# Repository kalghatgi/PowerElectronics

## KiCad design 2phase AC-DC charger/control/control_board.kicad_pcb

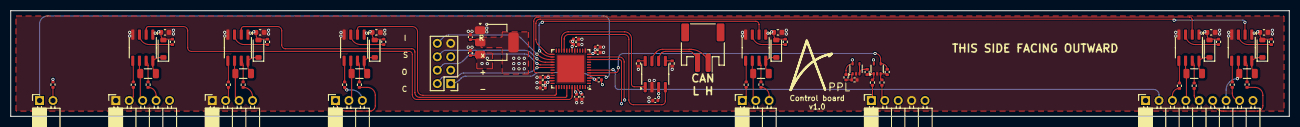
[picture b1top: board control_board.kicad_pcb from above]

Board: 4 copper layers, 242.0 x 20.0 mm, 78 parts (0 on the bottom side), 75 nets.

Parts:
C1, C2, C3, C4, C5, C6: 100nF, >=25V; C_1206_3216Metric
C7, C8, C14, C15, C16, C17, C18: 1uF, >=6.3V; C_0402_1005Metric
C9, C10: 10uF, >=6.3V; C_0402_1005Metric
C11, C13: 100nF, >=6.3V; C_0402_1005Metric
C12: 4.7uF, >=6.3V; C_0402_1005Metric
C19, C20, C21, C22, C23, C24: 10uF, >=25V; C_0603_1608Metric
D1, D2, D3, D4, D5, D6: Vr>=600V, If>=1A; D_SOD-123
IC1: F2800137RGZR; QFN-48-1EP_7x7mm_P0.5mm_EP5.1x5.1mm
J1: Conn_01x04_Socket; PinSocket_1x04_P2.54mm_Horizontal
J2, J6: Conn_01x04_Socket; PinSocket_1x05_P2.54mm_Horizontal
J3, J4: Conn_01x04_Socket; PinSocket_1x03_P2.54mm_Horizontal
J5: Conn_01x04_Socket; PinSocket_1x02_P2.54mm_Horizontal
J7: Conn_01x04_Socket; PinSocket_1x09_P2.54mm_Horizontal
J8: Conn_01x02_Pin; JST_PH_S2B-PH-SM4-TB_1x02-1MP_P2.00mm_Horizontal
J9: Conn_02x04_Counter_Clockwise; PinHeader_2x04_P2.54mm_Vertical
R1, R2, R3, R4, R5, R6, R7, R20, R21, R22, R23, R24, R25, R26, R27, R28: 10K, 62.5mW, 0402; R_0402_1005Metric
R8, R9, R10, R11, R12, R13, R14, R15, R16, R17, R18, R19: 4R, 62.5mW, 0402; R_0402_1005Metric
U1, U2, U3, U4, U5, U6: IR2104; SOIC-8_3.9x4.9mm_P1.27mm
U7: TCAN3414DR; SOIC-8_3.9x4.9mm_P1.27mm
U8: LD1117S12TR_SOT223; SOT-223-3_TabPin2
U9, U10: LMV321; SOT-353_SC-70-5

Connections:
+1.2V: C10.1, C15.1, C16.1, C17.1, C18.1, IC1.18 (VDDA), IC1.34 (VDDIO), IC1.45 (VDDIO), U8.2 (VO)
+3.3V: C7.1, C8.1, C9.1, C11.1, C12.1, C13.1, C14.1, IC1.12 (VREFHI), IC1.35 (VDD), IC1.44 (VDD), J6.3, J9.5, R7.1, R20.1, R21.1, U7.3 (VCC), U8.3 (VI), U9.5 (V+), U10.5 (V+)
+12V: C19.1, C20.1, C21.1, C22.1, C23.1, C24.1, D1.2 (A), D2.2 (A), D3.2 (A), D4.2 (A), D5.2 (A), D6.2 (A), J6.5, R1.1, R2.1, R3.1, R4.1, R5.1, R6.1, U1.1 (VCC), U2.1 (VCC), U3.1 (VCC), U4.1 (VCC), U5.1 (VCC), U6.1 (VCC)
/CAN_H: J8.1, U7.7 (CANH)
/CAN_L: J8.2, U7.6 (CANL)
/CAN_Rx: IC1.21 (A10/C10/GPIO230), U7.4 (RXD)
/CAN_Tx: IC1.22 (A19/C19/GPIO13), U7.1 (TXD)
/I_p: IC1.5 (A3/C5/GPIO242), R24.1, U10.4
/L_in: IC1.32 (GPIO18X2), U6.2 (IN)
/N_in: IC1.25 (GPIO16), U5.2 (IN)
/TCK: IC1.27 (TCK), J9.8
/TDI: IC1.30 (GPIO35/TDI), J9.2
/TDO: IC1.28 (GPIO37/TDO), J9.6
/TMS: IC1.29 (TMS), J9.4
/pA_in: IC1.26 (GPIO24), U3.2 (IN)
/pB_in: IC1.37 (GPIO4), U4.2 (IN)
/sA_in: IC1.43 (GPIO7), U1.2 (IN)
/sB_in: IC1.41 (GPIO0), U2.2 (IN)
/~RST: IC1.3 (XRSN), J9.1, R7.2
GND0: C7.2, C8.2, C9.2, C10.2, C11.2, C12.2, C13.2, C14.2, C15.2, C16.2, C17.2, C18.2, C19.2, C20.2, C21.2, C22.2, C23.2, C24.2, IC1.13 (VREFLO), IC1.17 (VSSA), IC1.49 (VSS), J1.1, J2.1, J6.4, J9.7, R22.2, R27.2, R28.2, U1.4 (COM), U2.4 (COM), U3.4 (COM), U4.4 (COM), U5.4 (COM), U6.4 (COM), U7.2 (GND), U8.1 (GND), U9.2 (V-), U10.2 (V-)
Ip_+: J6.2, R25.2
Ip_-: J6.1, R26.2
L_HG: J7.5, R13.1
L_HS: C6.2, J7.4, U6.6 (VS)
L_LG: J7.3, R16.1
N_HG: J7.6, R12.1
N_HS: C5.2, J7.7, U5.6 (VS)
N_LG: J7.8, R17.1
unnamed: C1.1, D1.1 (K), U1.8 (VB)
unnamed: C2.1, D2.1 (K), U2.8 (VB)
unnamed: C3.1, D3.1 (K), U3.8 (VB)
unnamed: C4.1, D4.1 (K), U4.8 (VB)
unnamed: C5.1, D5.1 (K), U5.8 (VB)
unnamed: C6.1, D6.1 (K), U6.8 (VB)
unnamed: R9.2, U1.7 (HO)
unnamed: R14.2, U1.5 (LO)
unnamed: R1.2, U1.3 (~SD)
unnamed: R8.2, U2.7 (HO)
unnamed: R19.2, U2.5 (LO)
unnamed: R2.2, U2.3 (~SD)
unnamed: R10.2, U3.7 (HO)
unnamed: R15.2, U3.5 (LO)
unnamed: R3.2, U3.3 (~SD)
unnamed: R11.2, U4.7 (HO)
unnamed: R18.2, U4.5 (LO)
unnamed: R4.2, U4.3 (~SD)
unnamed: R12.2, U5.7 (HO)
unnamed: R17.2, U5.5 (LO)
unnamed: R5.2, U5.3 (~SD)
unnamed: R13.2, U6.7 (HO)
unnamed: R16.2, U6.5 (LO)
unnamed: R6.2, U6.3 (~SD)
unnamed: R27.1, U7.5 (SHDN)
unnamed: R28.1, U7.8 (STB)
unnamed: R21.2, R22.1, U9.1 (+)
unnamed: R23.2, U9.3 (-), U9.4
unnamed: R23.1, R26.1, U10.1 (+)
unnamed: R24.2, R25.1, U10.3 (-)
V_batt_opto_in: J5.2, R20.2
V_battery: IC1.4 (A6/C6/GPIO226/GPIO228), J5.1
V_line: IC1.11 (A0/C15/CMP1_DACL), J7.1
V_neutral: IC1.10 (A1), J7.9
V_p: IC1.6 (A2/C9/GPIO224), J7.2
pA_HG: J3.3, R10.1
pA_HS: C3.2, J3.2, U3.6 (VS)
pA_LG: J3.1, R15.1
pB_HG: J4.1, R11.1
pB_HS: C4.2, J4.2, U4.6 (VS)
pB_LG: J4.3, R18.1
sA_HG: J2.4, R9.1
sA_HS: C1.2, J2.3, U1.6 (VS)
sA_LG: J2.2, R14.1
sB_HG: J1.4, R8.1
sB_HS: C2.2, J1.3, U2.6 (VS)
sB_LG: J1.2, R19.1

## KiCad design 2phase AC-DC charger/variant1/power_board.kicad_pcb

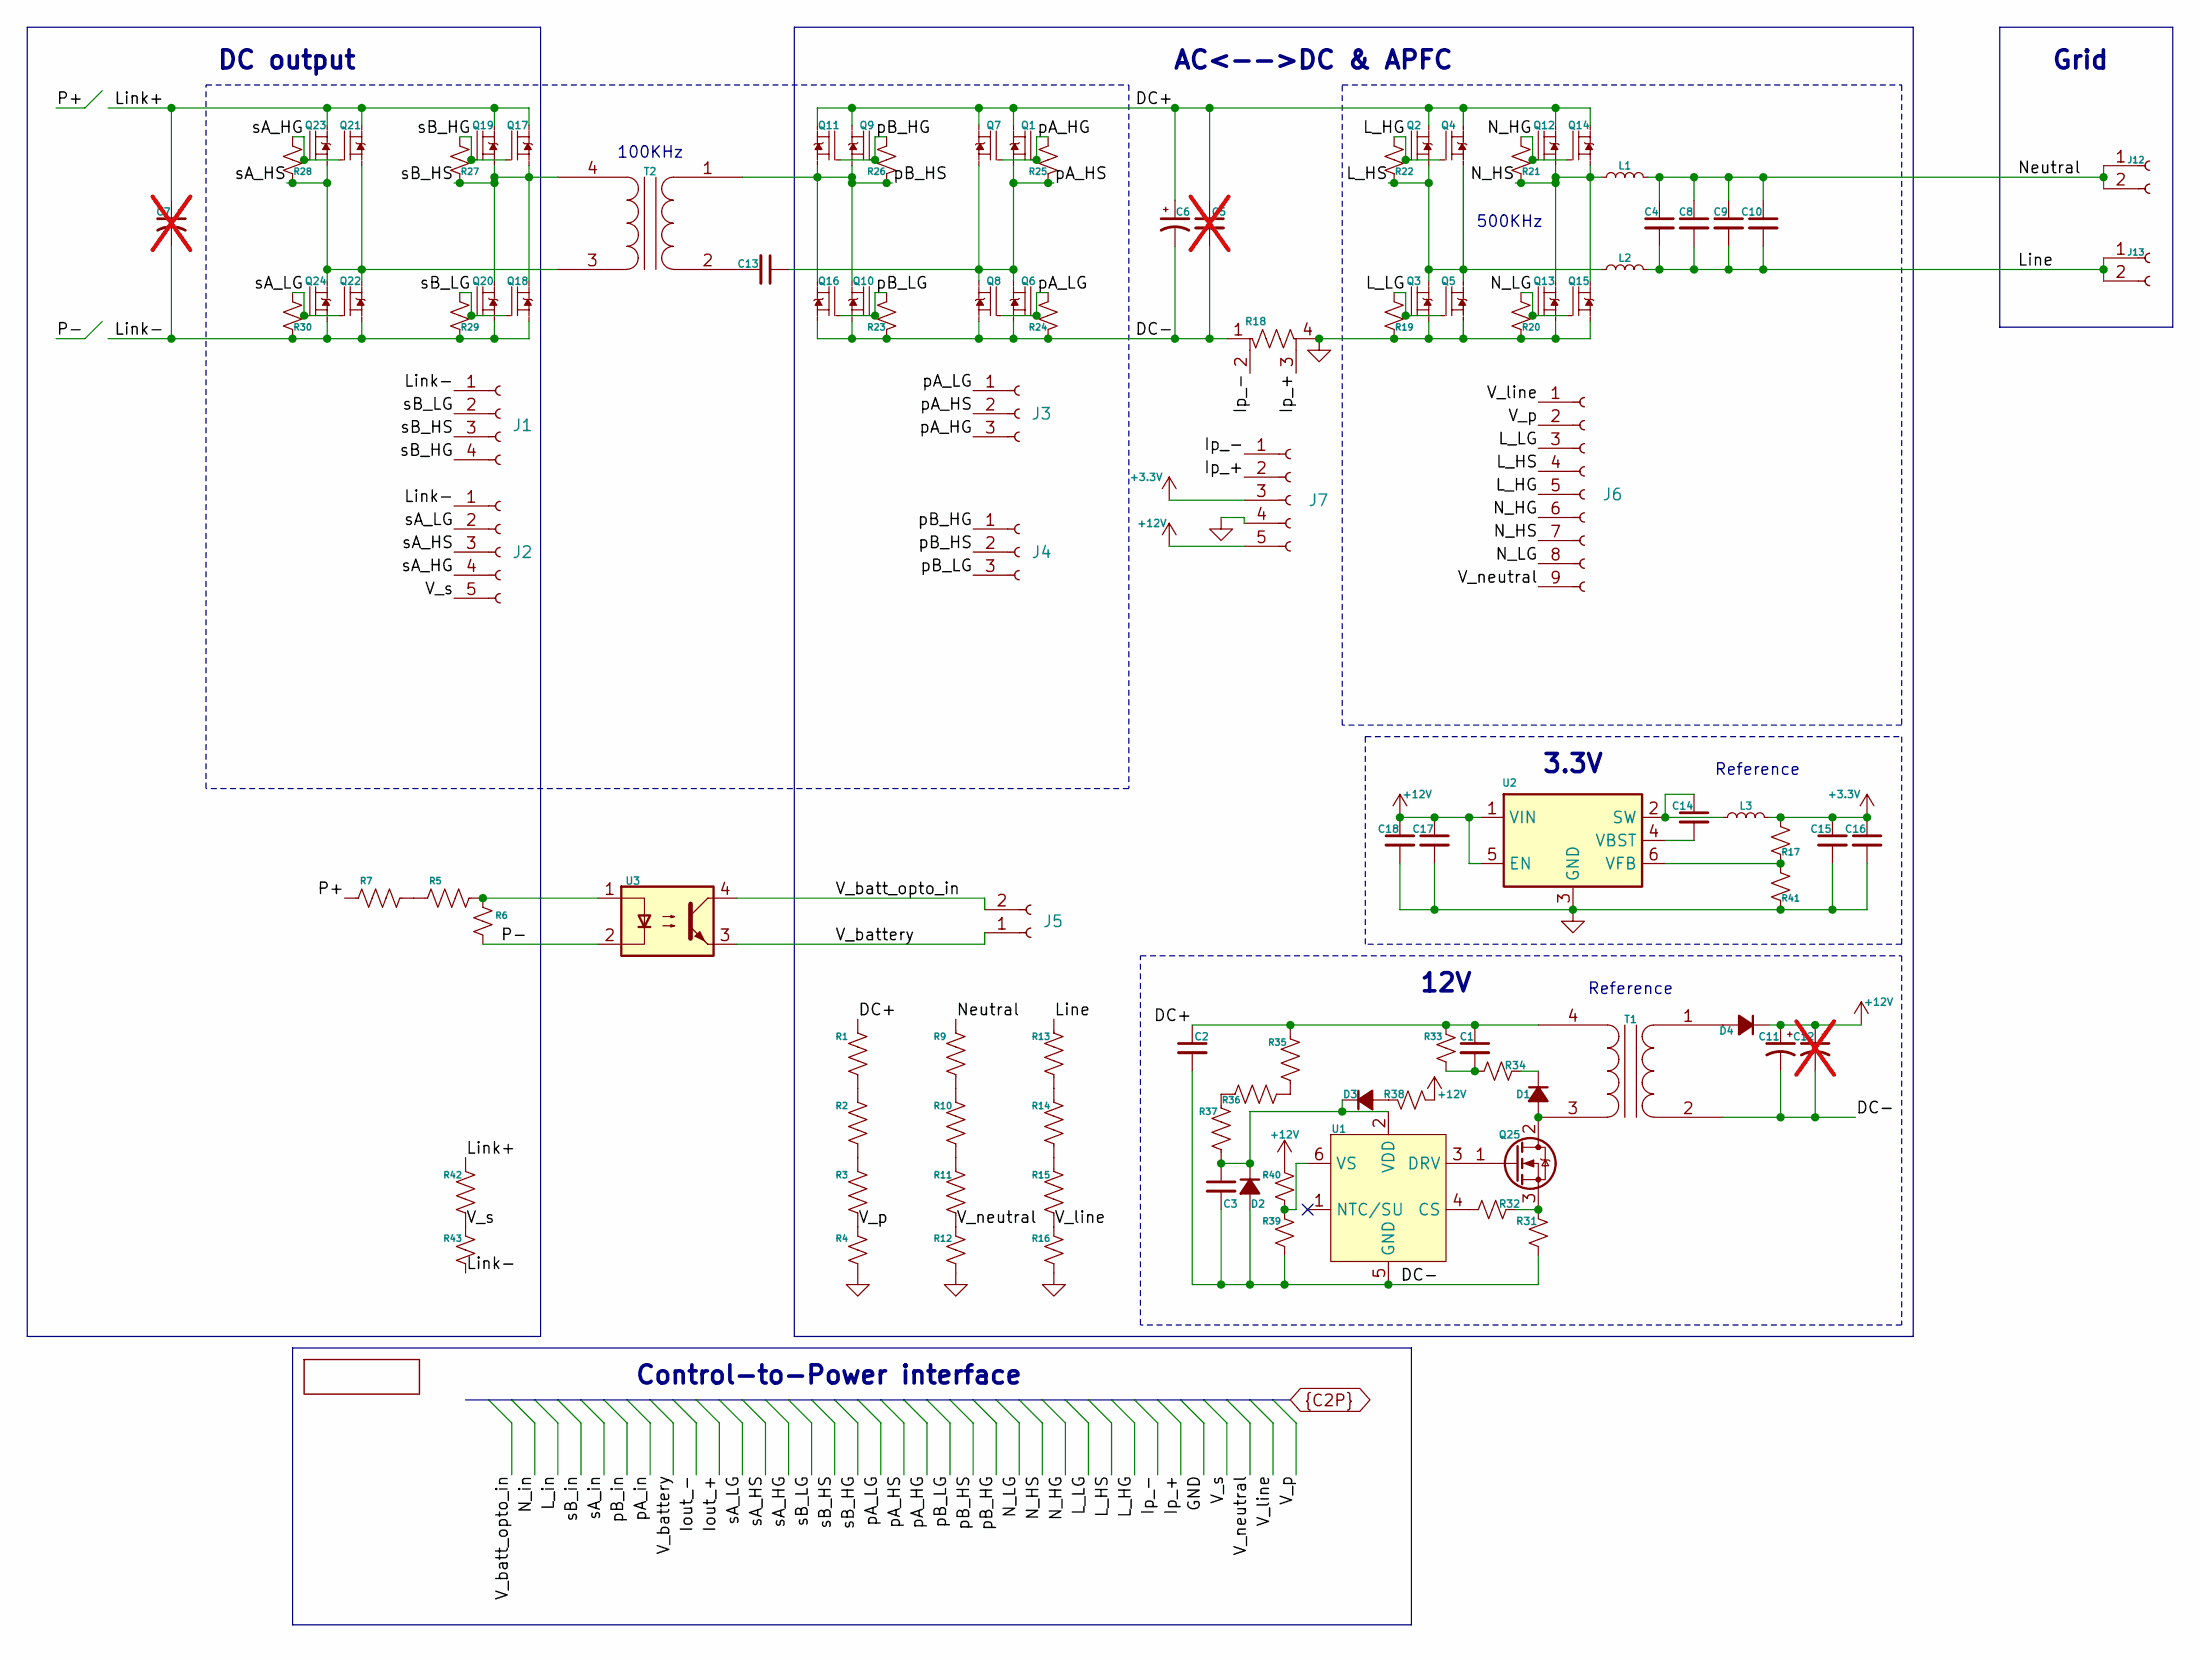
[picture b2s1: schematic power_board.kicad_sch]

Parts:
C1: 10nF, >450V; C_0805_2012Metric; MPN 885342207014
C2: 22nF, >=600V; C_2220_5750Metric
C3: 4.7uF, >=25V, 0603; C_0603_1608Metric
C4, C8, C9, C10: >2.2uF, >450V; C_2220_5750Metric; MPN C5750X6S2W225K250KA
C5: >4.7uF, >500V; C_2220_5750Metric; not fitted
C6: >25uF, >500V; C_Radial_D10.0mm_H12.5mm_P5.00mm
C7: 100uF, >60V; CP_Radial_D8.0mm_P3.50mm; MPN REF0812101M063K; not fitted
C11: 470uF, 25V; C_Radial_D8.0mm_H11.5mm_P3.50mm; MPN 860020474014
C12: 470uF, 25V; C_Radial_D8.0mm_H11.5mm_P3.50mm; MPN 860020474014; not fitted
C13: >4.7uF, >500V; C_2220_5750Metric
C14, C17: 100nF, >=25V; C_0603_1608Metric
C15, C16: 22uF, >=6.3V; C_0603_1608Metric
C18: 10uF, >=25V; C_0603_1608Metric
D1: Vr>=600V, If>=1A; D_SOD-123
D2: Vbr=22V; D_SOD-123
D3: Vbr=100V, If>=0.1A; D_SOD-123
D4: Vbr>=20V, Vf<=1V, If>2A; D_SOD-123
J1: Conn_01x04_Header; PinHeader_1x04_P2.54mm_Vertical
J2, J7: Conn_01x05_Header; PinHeader_1x05_P2.54mm_Vertical
J3, J4: Conn_01x03_Header; PinHeader_1x03_P2.54mm_Vertical
J5: Conn_01x02_Header; PinHeader_1x02_P2.54mm_Vertical
J6: Conn_01x09_Header; PinHeader_1x09_P2.54mm_Vertical
J12, J13: 2pin, >400V, >20A; TE_62409-1; MPN DJ6112
L1, L2: 15uH, >23A; PQ2617BHA150K; MPN PQ2617BHA-150K
L3: 3.3uH, >=0.5A; L_0805_2012Metric; MPN LQM21PN3R3NGRD
Q1, Q2, Q3, Q4, Q5, Q6, Q7, Q8, Q9, Q10, Q11, Q12, Q13, Q14, Q15, Q16: NMOS, Vds>=400V, Rds<=50mOhm; IPDQ60R037CM8XTMA1; MPN IPDQ60R037CM8XTMA1
Q17, Q18, Q19, Q20, Q21, Q22, Q23, Q24: NMOS, Vds>=40V, Rds<=1mOhm; Infineon_PG-TDSON-8_6.15x5.15mm; MPN IAUCN04S7N005ATMA1
Q25: NMOS, Vds>=450V, Ids>=6A; TO-252-3_TabPin2; MPN IPD50R500CEAUMA1
R1, R2, R3, R5, R7, R9, R10, R11, R13, R14, R15, R42: 1MOhm, >200V, <1%, >62.5mW; R_1206_3216Metric
R4, R6, R12, R16, R43: 10K, >62.5mW; R_0603_1608Metric
R17: 30.9K, >62.5mW, 0402; R_0402_1005Metric
R18: 10mOhm, >=3W; R_shunt_2512_6332Metric; MPN CRA2512-FZ-R010ELF
R19, R20, R21, R22, R23, R24, R25, R26, R27, R28, R29, R30, R41: 10K, >62.5mW, 0402; R_0402_1005Metric
R31: 1.87R, 62.5mW, 0603; R_0603_1608Metric
R32: 1.91K, 62.5mW, 0402; R_0402_1005Metric
R33: 82K, >=2W, 0805; R_0805_2012Metric
R34: 51.1R, >62.5mW, 0402; R_0402_1005Metric
R35, R36, R37: 1.324MOhm, >200V, >62.5mW, 1206; R_1206_3216Metric
R38: 22.1R, >62.5mW, 0402; R_0402_1005Metric
R39: 32.4K, >62.5mW, 0402; R_0402_1005Metric
R40: 113K, >62.5mW, 0402; R_0402_1005Metric
T1: Np:Ns=130:9, Lmag=3.38mH
T2: Np:Ns=9:1, Lk=40uH, N87
U1: UC28704; SOT-23-6
U2: TPS562202; SOT-563
U3: ACPL-214-500E; DIP-4_W7.62mm

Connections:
+3.3V: C15.1, C16.1, J7.3, L3.1, R17.1
+12V: C11.1, C12.1, C17.1, C18.1, D4.1 (K), J7.5, R38.1, R40.1, U2.1 (VIN), U2.5 (EN)
/DC+: C1.1, C2.1, C5.1, C6.1, Q1.3 (D), Q2.3 (D), Q4.3 (D), Q7.3 (D), Q9.3 (D), Q11.3 (D), Q12.3 (D), Q14.3 (D), R1.1, R33.1, R35.1, T1.4 (SB)
/DC-: C2.2, C3.2, C5.2, C6.2, C11.2, C12.2, D2.2 (A), Q6.2 (S), Q8.2 (S), Q10.2 (S), Q16.2 (S), R18.1, R23.2, R24.2, R31.2, R39.2, T1.2 (AB), U1.5 (GND)
/Line: C4.2, C8.2, C9.2, C10.2, J13.1, J13.2, L2.2, R13.1
/Link+: C7.1, Q17.5 (D), Q19.5 (D), Q21.5 (D), Q23.5 (D), R42.1
/Link-: C7.2, J1.1, J2.1, Q18.2 (S), Q18.3 (S), Q18.4 (S), Q20.2 (S), Q20.3 (S), Q20.4 (S), Q22.2 (S), Q22.3 (S), Q22.4 (S), Q24.2 (S), Q24.3 (S), Q24.4 (S), R29.2, R30.2, R43.2
/Neutral: C4.1, C8.1, C9.1, C10.1, J12.1, J12.2, L1.1, R9.1
/P+: R7.1
/P-: R6.2, U3.2
GND0: C15.2, C16.2, C17.2, C18.2, J7.4, Q3.2 (S), Q5.2 (S), Q13.2 (S), Q15.2 (S), R4.2, R12.2, R16.2, R18.4, R19.2, R20.2, R41.2, U2.3 (GND)
Ip_+: J7.2, R18.3
Ip_-: J7.1, R18.2
L_HG: J6.5, Q2.1 (G), Q4.1 (G), R22.1
L_HS: J6.4, L2.1, Q2.2 (S), Q3.3 (D), Q4.2 (S), Q5.3 (D), R22.2
L_LG: J6.3, Q3.1 (G), Q5.1 (G), R19.1
N_HG: J6.6, Q12.1 (G), Q14.1 (G), R21.1
N_HS: J6.7, L1.2, Q12.2 (S), Q13.3 (D), Q14.2 (S), Q15.3 (D), R21.2
N_LG: J6.8, Q13.1 (G), Q15.1 (G), R20.1
unnamed: C1.2, R33.2, R34.1
unnamed: D1.2 (A), Q25.2 (D), T1.3 (SA)
unnamed: D1.1 (K), R34.2
unnamed: C3.1, D2.1 (K), D3.1 (K), R37.2, U1.2 (VDD)
unnamed: D3.2 (A), R38.2
unnamed: D4.2 (A), T1.1 (AA)
unnamed: Q25.1 (G), U1.3 (DRV)
unnamed: Q25.3 (S), R31.1, R32.2
unnamed: R1.2, R2.1
unnamed: R2.2, R3.1
unnamed: R5.1, R7.2
unnamed: R5.2, R6.1, U3.1
unnamed: R9.2, R10.1
unnamed: R10.2, R11.1
unnamed: R13.2, R14.1
unnamed: R14.2, R15.1
unnamed: R35.2, R36.1
unnamed: R36.2, R37.1
unnamed: C13.2, T2.2 (AB)
unnamed: R32.1, U1.4 (CS)
unnamed: R39.1, R40.2, U1.6 (VS)
unnamed: C14.1, L3.2, U2.2 (SW)
unnamed: C14.2, U2.4 (VBST)
unnamed: R17.2, R41.1, U2.6 (VFB)
V_batt_opto_in: J5.2, U3.4
V_battery: J5.1, U3.3
V_line: J6.1, R15.2, R16.1
V_neutral: J6.9, R11.2, R12.1
V_p: J6.2, R3.2, R4.1
V_s: J2.5, R42.2, R43.1
pA_HG: J3.3, Q1.1 (G), Q7.1 (G), R25.1
pA_HS: C13.1, J3.2, Q1.2 (S), Q6.3 (D), Q7.2 (S), Q8.3 (D), R25.2
pA_LG: J3.1, Q6.1 (G), Q8.1 (G), R24.1
pB_HG: J4.1, Q9.1 (G), Q11.1 (G), R26.1
pB_HS: J4.2, Q9.2 (S), Q10.3 (D), Q11.2 (S), Q16.3 (D), R26.2, T2.1 (AA)
pB_LG: J4.3, Q10.1 (G), Q16.1 (G), R23.1
sA_HG: J2.4, Q21.1 (G), Q23.1 (G), R28.1
sA_HS: J2.3, Q21.2 (S), Q21.3 (S), Q21.4 (S), Q22.5 (D), Q23.2 (S), Q23.3 (S), Q23.4 (S), Q24.5 (D), R28.2, T2.3 (SA)
sA_LG: J2.2, Q22.1 (G), Q24.1 (G), R30.1
sB_HG: J1.4, Q17.1 (G), Q19.1 (G), R27.1
sB_HS: J1.3, Q17.2 (S), Q17.3 (S), Q17.4 (S), Q18.5 (D), Q19.2 (S), Q19.3 (S), Q19.4 (S), Q20.5 (D), R27.2, T2.4 (SB)
sB_LG: J1.2, Q18.1 (G), Q20.1 (G), R29.1

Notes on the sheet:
500KHz
Reference
AC<-->DC & APFC
DC output
Grid
Control-to-Power interface
12V
100KHz
3.3V

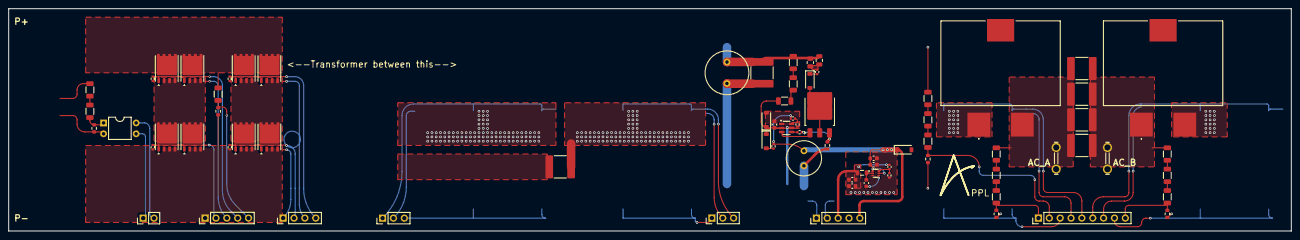
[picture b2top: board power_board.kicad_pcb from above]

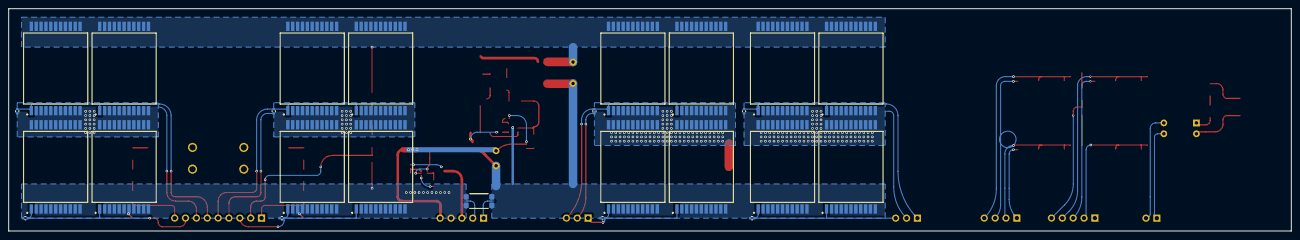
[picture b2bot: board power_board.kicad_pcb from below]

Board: 2 copper layers, 300.0 x 52.0 mm, 101 parts (25 on the bottom side), 58 nets.

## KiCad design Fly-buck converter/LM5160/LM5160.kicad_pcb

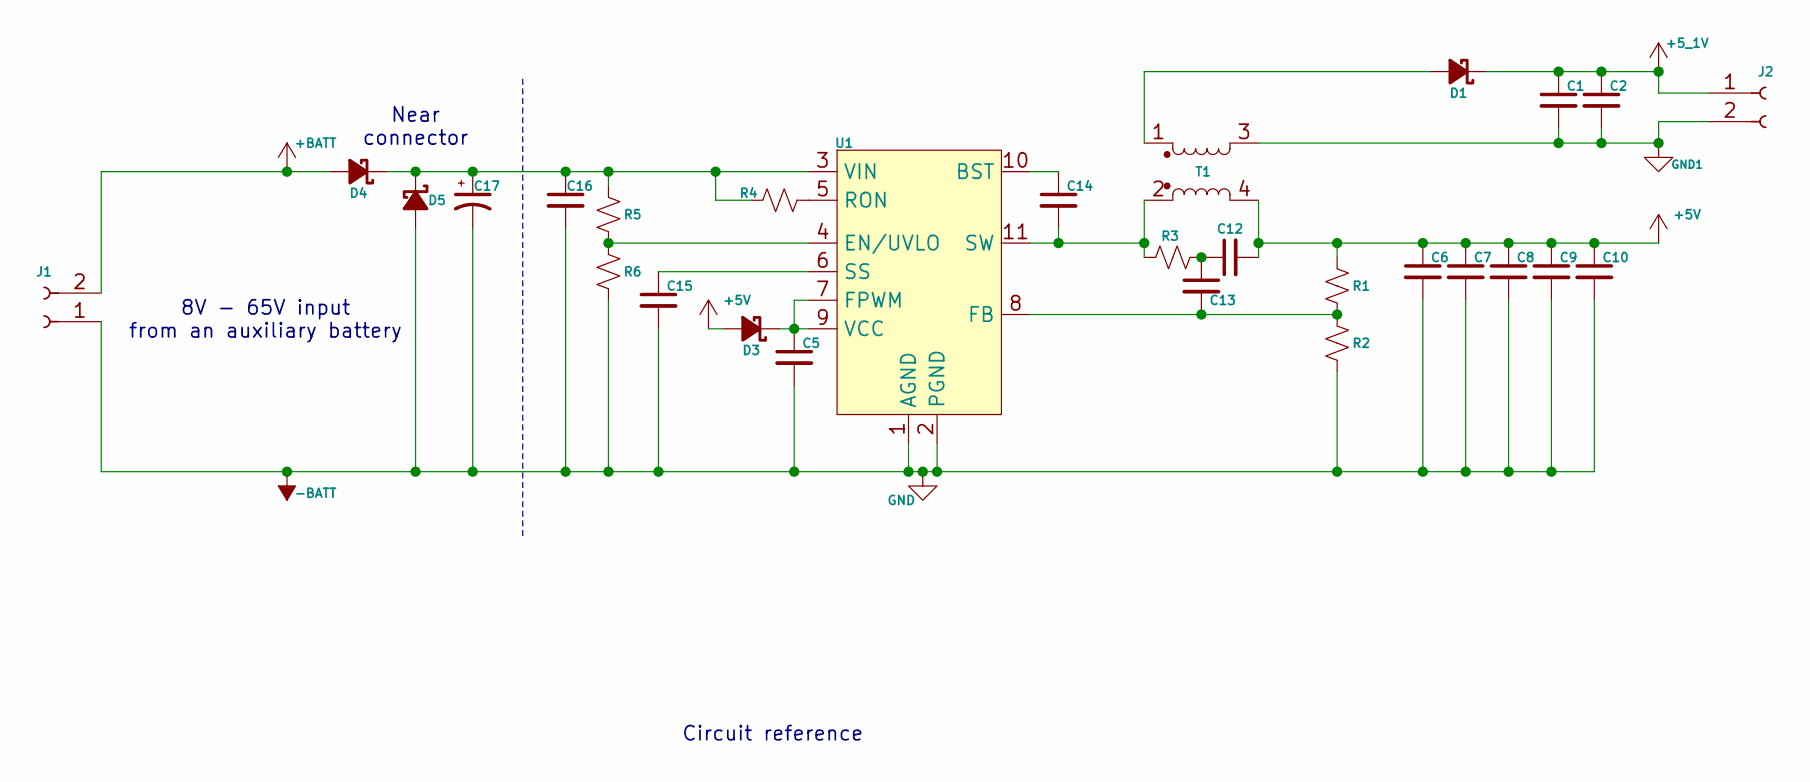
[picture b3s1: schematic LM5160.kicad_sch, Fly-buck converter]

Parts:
C1, C2, C6, C7, C8, C9, C10: 10uF, 25V, 0603; C_0603_1608Metric
C5: 1uF, 25V, 0603; C_0603_1608Metric
C12: 3.9nF, 10V, 0402; C_0402_1005Metric
C13: 15nF, 10V, 0402; C_0402_1005Metric
C14: 10nF, 25V, 0603; C_0603_1608Metric
C15: 22nF, 10V, 0402; C_0402_1005Metric
C16: 1uF, 80V, 0805; C_0805_2012Metric
C17: 22uF 75V; CP_Elec_10x10.5
D1, D5: Vstandoff=60V, Vbreakdown=65V, Iforward=1A; D_SOD-123
D3: Vstandoff=60V, Vbreakdown=65V, Iforward=0.1A; D_SOD-123
D4: Vstandoff=190V, Vbreakdown=200V, Iforward=1A; D_SOD-123
J1, J2: Conn_01x02_Socket; Molex_Micro-Fit_3.0_43650-0200_1x02_P3.00mm_Horizontal
R1: 2.26K, 0.0625W, 0402; R_0402_1005Metric
R2: 1.5K, 0.0625W, 0402; R_0402_1005Metric
R3: 75K, 0.0625W, 0402; R_0402_1005Metric
R4: 205K, 0.100W, 0402; R_0402_1005Metric
R5: 133K, 0.100W, 0603; R_0603_1608Metric
R6: 12.1K, 0.100W, 0402; R_0402_1005Metric
T1: 47uH, DCR=86mOhm; L_Bourns_SRF1260; MPN srf1260-470m
U1: LM5160; WSON-12-1EP_4x4mm_P0.5mm_EP2.6x3mm_ThermalVias

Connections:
+5V: C6.1, C7.1, C8.1, C9.1, C10.1, C12.2, D3.2 (A), R1.1, T1.4
+5_1V: C1.1, C2.1, D1.1 (K), J2.1
+BATT: D4.2 (A), J1.2
-BATT: C5.2, C6.2, C7.2, C8.2, C9.2, C10.2, C15.2, C16.2, C17.2, D5.2 (A), J1.1, R2.2, R6.2, U1.1 (AGND), U1.2 (PGND), U1.13 (EP)
GND1: C1.2, C2.2, J2.2, T1.3
unnamed: C12.1, C13.1, R3.2
unnamed: C14.2, R3.1, T1.2, U1.11 (SW), U1.12 (SW)
unnamed: D1.2 (A), T1.1
unnamed: C5.1, D3.1 (K), U1.7 (FPWM), U1.9 (VCC)
unnamed: C16.1, C17.1, D4.1 (K), D5.1 (K), R4.1, R5.1, U1.3 (VIN)
unnamed: C14.1, U1.10 (BST)
unnamed: R5.2, R6.1, U1.4 (EN/UVLO)
unnamed: C13.2, R1.2, R2.1, U1.8 (FB)
unnamed: R4.2, U1.5 (RON)
unnamed: C15.1, U1.6 (SS)

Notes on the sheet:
8V - 65V input from an auxiliary battery
Near connector
Circuit reference

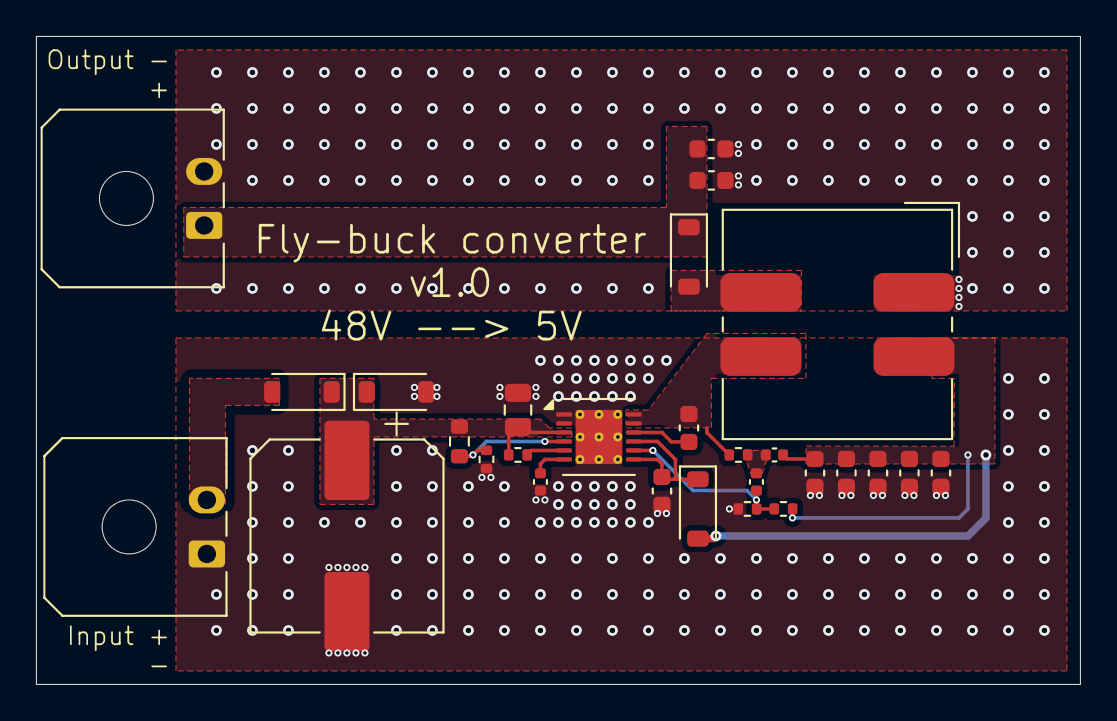
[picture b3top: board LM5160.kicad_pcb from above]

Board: 2 copper layers, 58.0 x 36.0 mm, 28 parts (0 on the bottom side), 15 nets.

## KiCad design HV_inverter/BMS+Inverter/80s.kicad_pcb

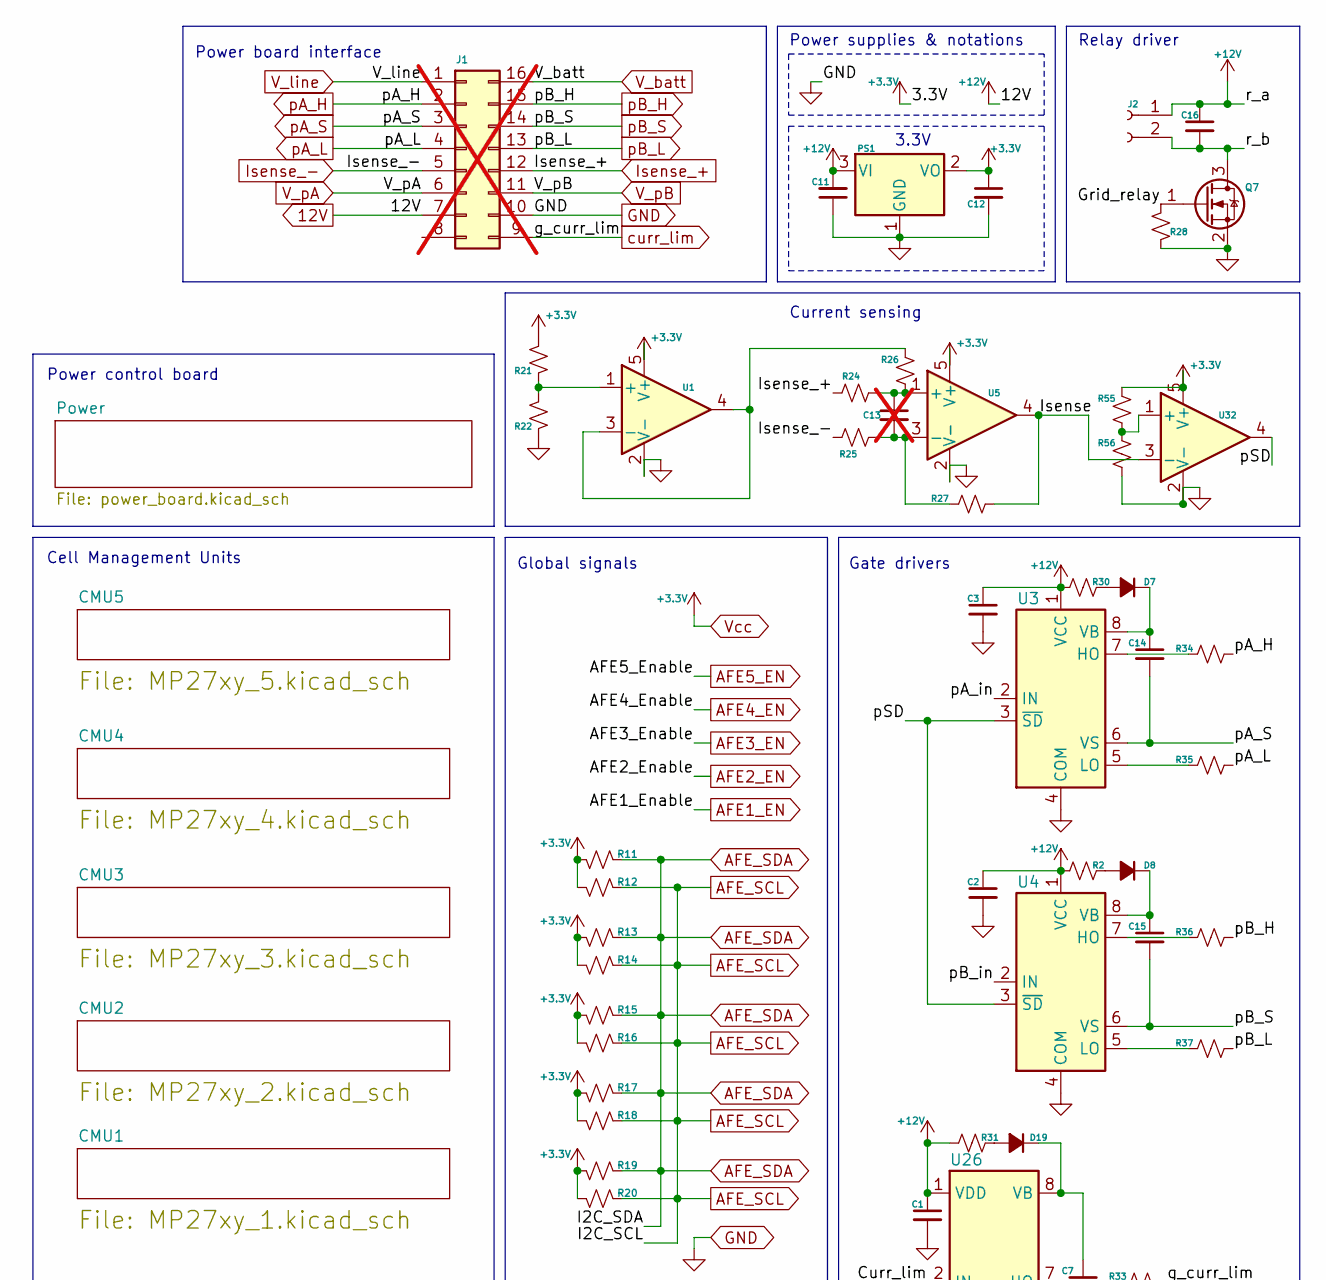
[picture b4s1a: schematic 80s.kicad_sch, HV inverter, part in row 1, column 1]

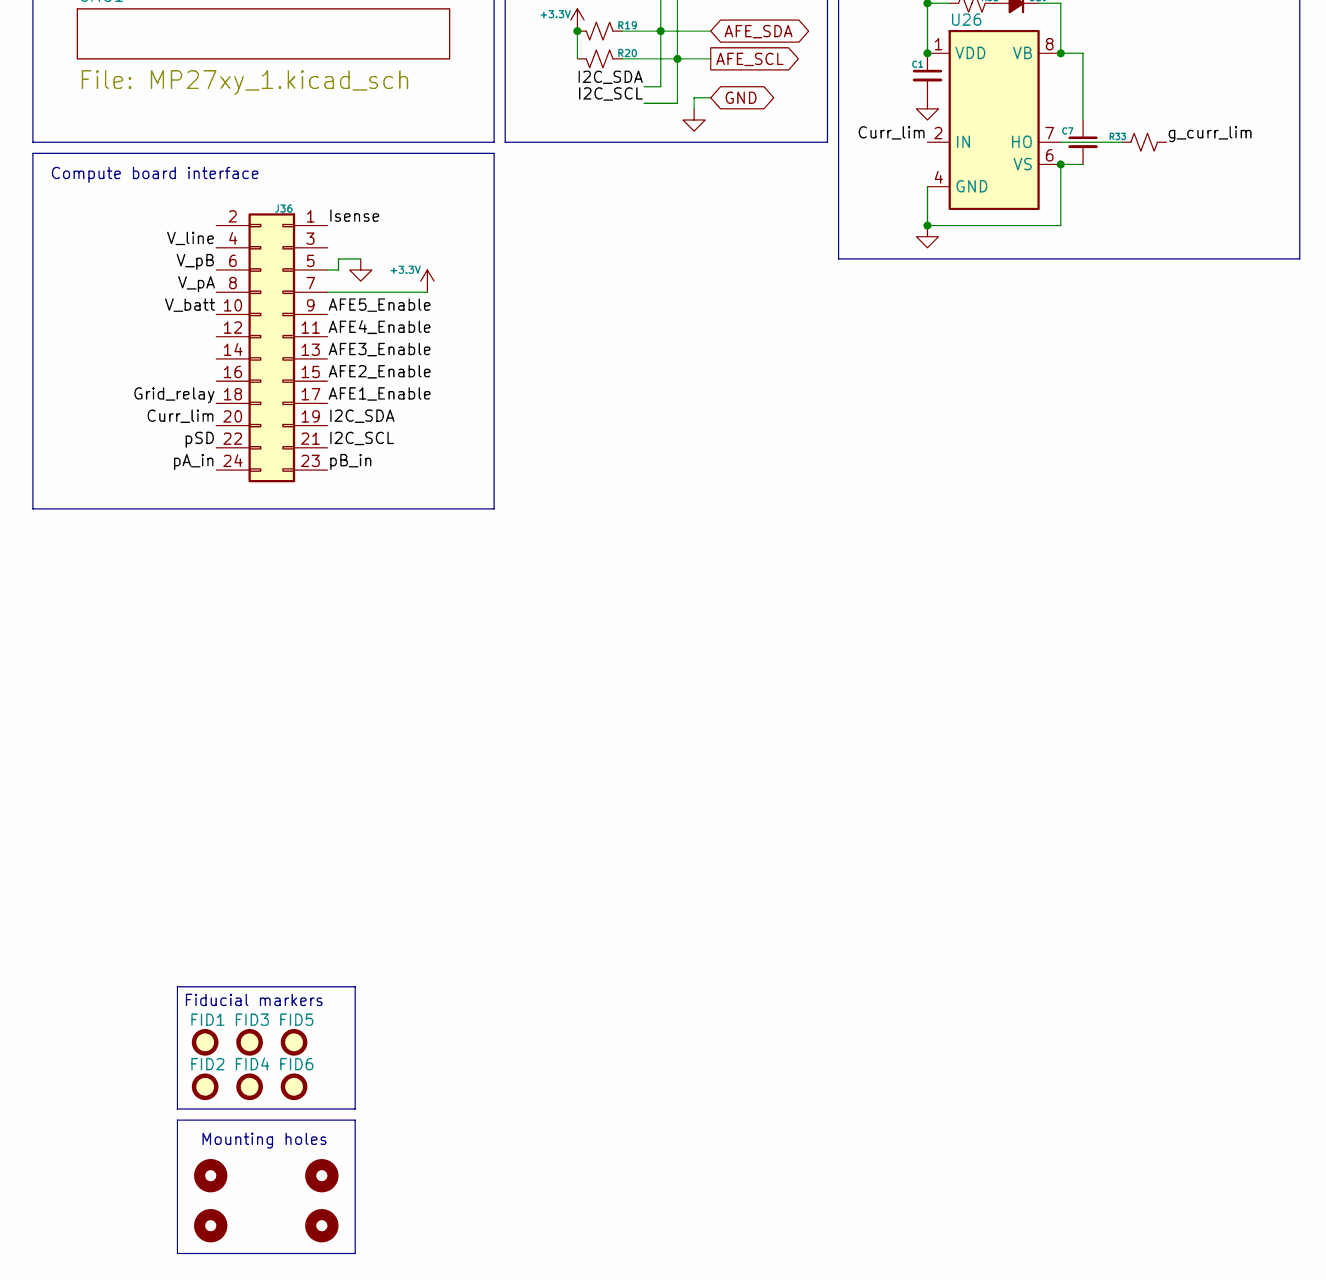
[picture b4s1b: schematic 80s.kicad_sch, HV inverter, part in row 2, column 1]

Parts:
C1, C2, C3: 10uF, >=25V, 0402; C_0402_1005Metric
C7, C14, C15: 1uF, >=25V, 0603; C_0805_2012Metric; MPN cl05a105kp5nnnc
C11: 22uF, >=25V, 0603; C_0603_1608Metric; MPN grm21br61e226me44k
C12: 10uF, >=10V, 0402; C_0402_1005Metric; MPN grm155r61a106me11d
C13: 4700pF, >=10V, 0402; C_0402_1005Metric; MPN mc0402b472k250ct; not fitted
C16: 10uF, >=30V, 0603; C_0603_1608Metric; MPN grm188r6ya106ma73d
D7, D8: Vr>400V, If>0.2A; D_PowerDI-123; MPN SBR1U400P1-7
D19: Vr>400V, If>0.2A; D_SOD-123; MPN BAV19W-E3-08
FID1, FID2, FID3, FID4, FID5, FID6: Fiducial; Fiducial_1.5mm_Mask3mm
H1, H2, H3, H4: M3 screw holes; MountingHole_3.2mm_M3; MPN 6532, 7080, 6534
J1: 2x7 pin, 2.54mm pitch; PinSocket_2x07_P2.54mm_Vertical; not fitted
J2: Conn_01x02_Socket; JST_PH_B2B-PH-K_1x02_P2.00mm_Vertical
J36: 2x7 pin, 2.54mm pitch; PinSocket_2x12_P1.27mm_Vertical_SMD
PS1: Vin_min>=3.8V, Vout=3.3V, Iout>=0.2A, SOT-223-3; SOT-223-3_TabPin2; MPN ap2114h-3-3trg1
Q7: NMOS, >=20V, >=4A; SOT-23; MPN dmn3404l-7
R2, R30, R31, R33, R34, R35, R36, R37: 3R, >=62.5mW, 0402; R_0402_1005Metric
R11, R12, R13, R14, R15, R16, R17, R18, R19, R20: 1.5K, >=62.5mW, 0402; R_0402_1005Metric; MPN mcwr04x1501ftl
R21, R22: 240K, >=62.5mW, 0402; R_0402_1005Metric; MPN mcwr04x2403ftl
R24, R25: 100R, >=62.5mW, 0402; R_0402_1005Metric; MPN mcwr04x1000ftl
R26, R27: 1.3K, >=62.5mW, 0402; R_0402_1005Metric
R28: 10K, >=62.5mW, 0402; R_0402_1005Metric; MPN mcwr04x1002ftl
R55: 1K, >=62.5mW, 0402; R_0402_1005Metric
R56: 10K, >=62.5mW, 0402; R_0402_1005Metric
U1, U5, U32: 5V OPAMP SOT-325; SOT-353_SC-70-5; MPN lmv321seg-7
U3, U4: IR2104; SOIC-8_3.9x4.9mm_P1.27mm
U26: FAN7371; SOIC-8_3.9x4.9mm_P1.27mm

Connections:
12V: C1.1, C2.1, C3.1, C11.2, C16.1, J1.7, J2.1, PS1.3 (VI), R2.1, R30.1, R31.1, U3.1 (VCC), U4.1 (VCC), U26.1 (VDD); also elsewhere on the board
/Curr_lim: J36.20, U26.2 (IN)
/Grid_relay: J36.18, Q7.1 (G), R28.1
/Isense: J36.1, R27.2, U5.4, U32.3 (-)
/pA_in: J36.24, U3.2 (IN)
/pB_in: J36.23, U4.2 (IN)
/pSD: J36.22, U3.3 (~SD), U4.3 (~SD), U32.4
/r_b: C16.2, J2.2, Q7.3 (D)
AFE1_EN: J36.17; also elsewhere on the board
AFE2_EN: J36.15; also elsewhere on the board
AFE3_EN: J36.13; also elsewhere on the board
AFE4_EN: J36.11; also elsewhere on the board
AFE5_EN: J36.9; also elsewhere on the board
AFE_SCL: J36.21, R12.2, R14.2, R16.2, R18.2, R20.2; also elsewhere on the board
AFE_SDA: J36.19, R11.2, R13.2, R15.2, R17.2, R19.2; also elsewhere on the board
GND: C1.2, C2.2, C3.2, C7.2, C11.1, C12.2, J1.10, J36.5, PS1.1 (GND), Q7.2 (S), R22.2, R28.2, R56.1, U1.2 (V-), U3.4 (COM), U4.4 (COM), U5.2 (V-), U26.4 (GND), U26.6 (VS), U32.2 (V-); also elsewhere on the board
Isense_+: J1.12, R24.1; also elsewhere on the board
Isense_-: J1.5, R25.1; also elsewhere on the board
unnamed: D7.2 (A), R30.2
unnamed: C14.1, D7.1 (K), U3.8 (VB)
unnamed: D8.2 (A), R2.2
unnamed: C15.1, D8.1 (K), U4.8 (VB)
unnamed: D19.2 (A), R31.2
unnamed: C7.1, D19.1 (K), U26.8 (VB)
unnamed: R21.2, R22.1, U1.1 (+)
unnamed: R26.2, U1.3 (-), U1.4
unnamed: R34.1, U3.7 (HO)
unnamed: R35.1, U3.5 (LO)
unnamed: R36.1, U4.7 (HO)
unnamed: R37.1, U4.5 (LO)
unnamed: C13.1, R24.2, R26.1, U5.1 (+)
unnamed: C13.2, R25.2, R27.1, U5.3 (-)
unnamed: R33.1, U26.7 (HO)
unnamed: R55.1, R56.2, U32.1 (+)
V_batt: J1.16, J36.10; also elsewhere on the board
V_line: J1.1, J36.4; also elsewhere on the board
V_pA: J1.6, J36.8; also elsewhere on the board
V_pB: J1.11, J36.6; also elsewhere on the board
Vcc: C12.1, J36.7, PS1.2 (VO), R11.1, R12.1, R13.1, R14.1, R15.1, R16.1, R17.1, R18.1, R19.1, R20.1, R21.1, R55.2, U1.5 (V+), U5.5 (V+), U32.5 (V+); also elsewhere on the board
curr_lim: J1.9, R33.2; also elsewhere on the board
pA_H: J1.2, R34.2; also elsewhere on the board
pA_L: J1.4, R35.2; also elsewhere on the board
pA_S: C14.2, J1.3, U3.6 (VS); also elsewhere on the board
pB_H: J1.15, R36.2; also elsewhere on the board
pB_L: J1.13, R37.2; also elsewhere on the board
pB_S: C15.2, J1.14, U4.6 (VS); also elsewhere on the board

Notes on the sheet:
Mounting holes
3.3V
Gate drivers
Compute board interface
Power board interface
Power control board
Current sensing
Relay driver
Power supplies & notations
Fiducial markers
Global signals
Cell Management Units
